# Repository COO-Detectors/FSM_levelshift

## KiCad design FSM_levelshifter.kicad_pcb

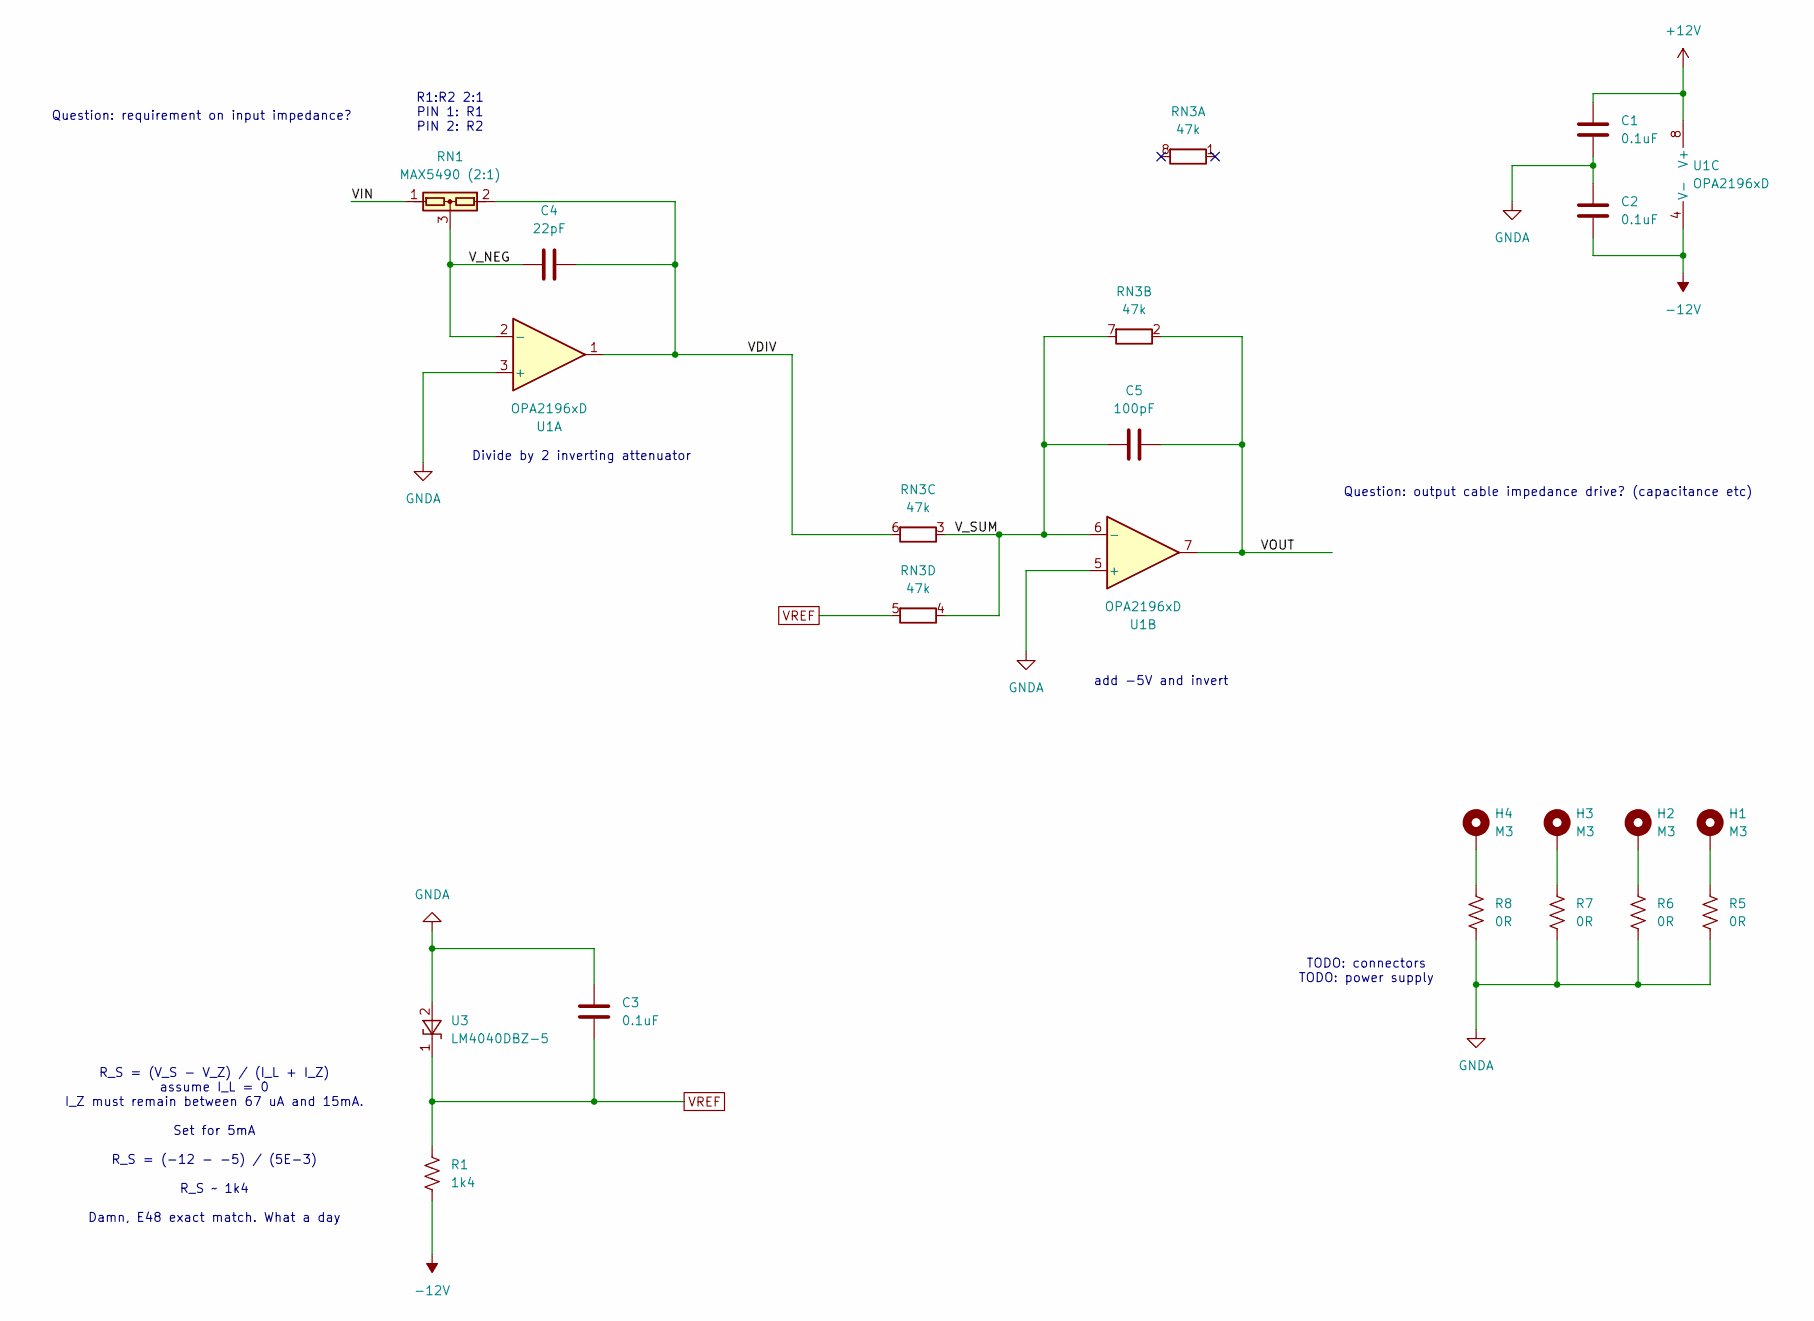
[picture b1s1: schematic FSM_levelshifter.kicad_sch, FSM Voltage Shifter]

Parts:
C1, C2, C3: 0.1uF; C_0603_1608Metric
C4: 22pF; C_0603_1608Metric
C5: 100pF; C_0603_1608Metric
H1, H2, H3, H4: M3; MountingHole_3.2mm_M3_Pad
R1: 1k4; R_0603_1608Metric
R5, R6, R7, R8: 0R; R_0603_1608Metric
RN1: MAX5490 (2:1); SOT-23; MPN MAX5490MA02000+T
RN3: 47k; RESCAXS80P320X160X60-8N; MPN EXB-38V473JV
U1: OPA2196xD; SOIC-8_3.9x4.9mm_P1.27mm; MPN OPA2196IDR
U3: LM4040DBZ-5; SOT-23

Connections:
+12V: C1.1, U1.8 (V+)
-12V: C2.2, R1.2, U1.4 (V-)
/VDIV: C4.2, RN1.2, RN3.6 (R3.2), U1.1
/VIN: RN1.1
/VOUT: C5.2, RN3.2 (R2.1), U1.7
/V_NEG: C4.1, RN1.3, U1.2 (-)
/V_SUM: C5.1, RN3.3 (R3.1), RN3.4 (R4.1), RN3.7 (R2.2), U1.6 (-)
GNDA: C1.2, C2.1, C3.1, R5.2, R6.2, R7.2, R8.2, U1.3 (+), U1.5 (+), U3.2 (A)
unnamed: H1.1 (1_1), R5.1
unnamed: H2.1 (1_1), R6.1
unnamed: H3.1 (1_1), R7.1
unnamed: H4.1 (1_1), R8.1
VREF: C3.2, R1.1, RN3.5 (R4.2), U3.1 (K)

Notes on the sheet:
Question: output cable impedance drive? (capacitance etc)
Divide by 2 inverting attenuator
R_S = (V_S - V_Z) / (I_L + I_Z) assume I_L = 0 I_Z must remain between 67 uA and 15mA. Set for 5mA R_S = (-12 - -5) / (5E-3) R_S ~ 1k4 Damn, E48 exact match. What a day
R1:R2 2:1 PIN 1: R1 PIN 2: R2
TODO: connectors TODO: power supply
Question: requirement on input impedance?
add -5V and invert

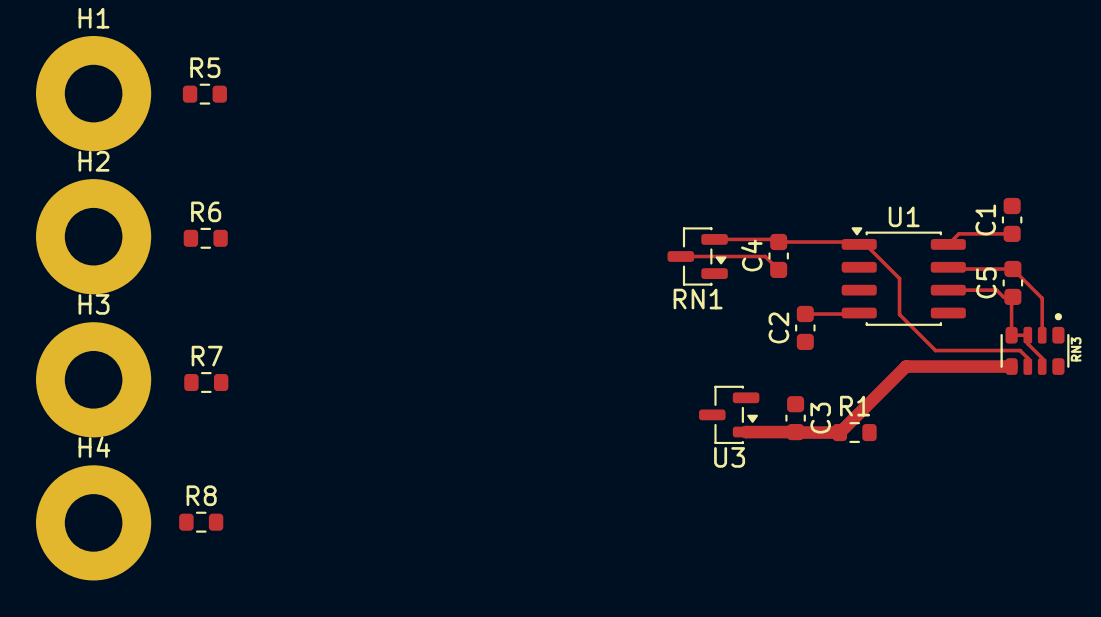
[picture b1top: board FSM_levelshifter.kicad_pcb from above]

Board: 4 copper layers, 18 parts (0 on the bottom side), 12 nets.
